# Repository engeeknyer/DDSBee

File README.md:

# DDSBee
## microcontrolled DDS oscillator circuit with XBee footprint

This directory contains the technical and constructive report for a microcontrolled DDS oscillator circuit. The onboard microcontroller allows the programming of the oscillator in a versatile way, using an instruction set close to the user’s language. The circuit is compatible with XBee footprint. Moreover the document also contains the user documentation and examples for proper use.
The device is intended to be a basic building block for a wide range of applications, thus easing the process of electronic system’s engineering. It exhibits remarkable degrees of flexibility, which makes it amenable to a wide range of possible applications.

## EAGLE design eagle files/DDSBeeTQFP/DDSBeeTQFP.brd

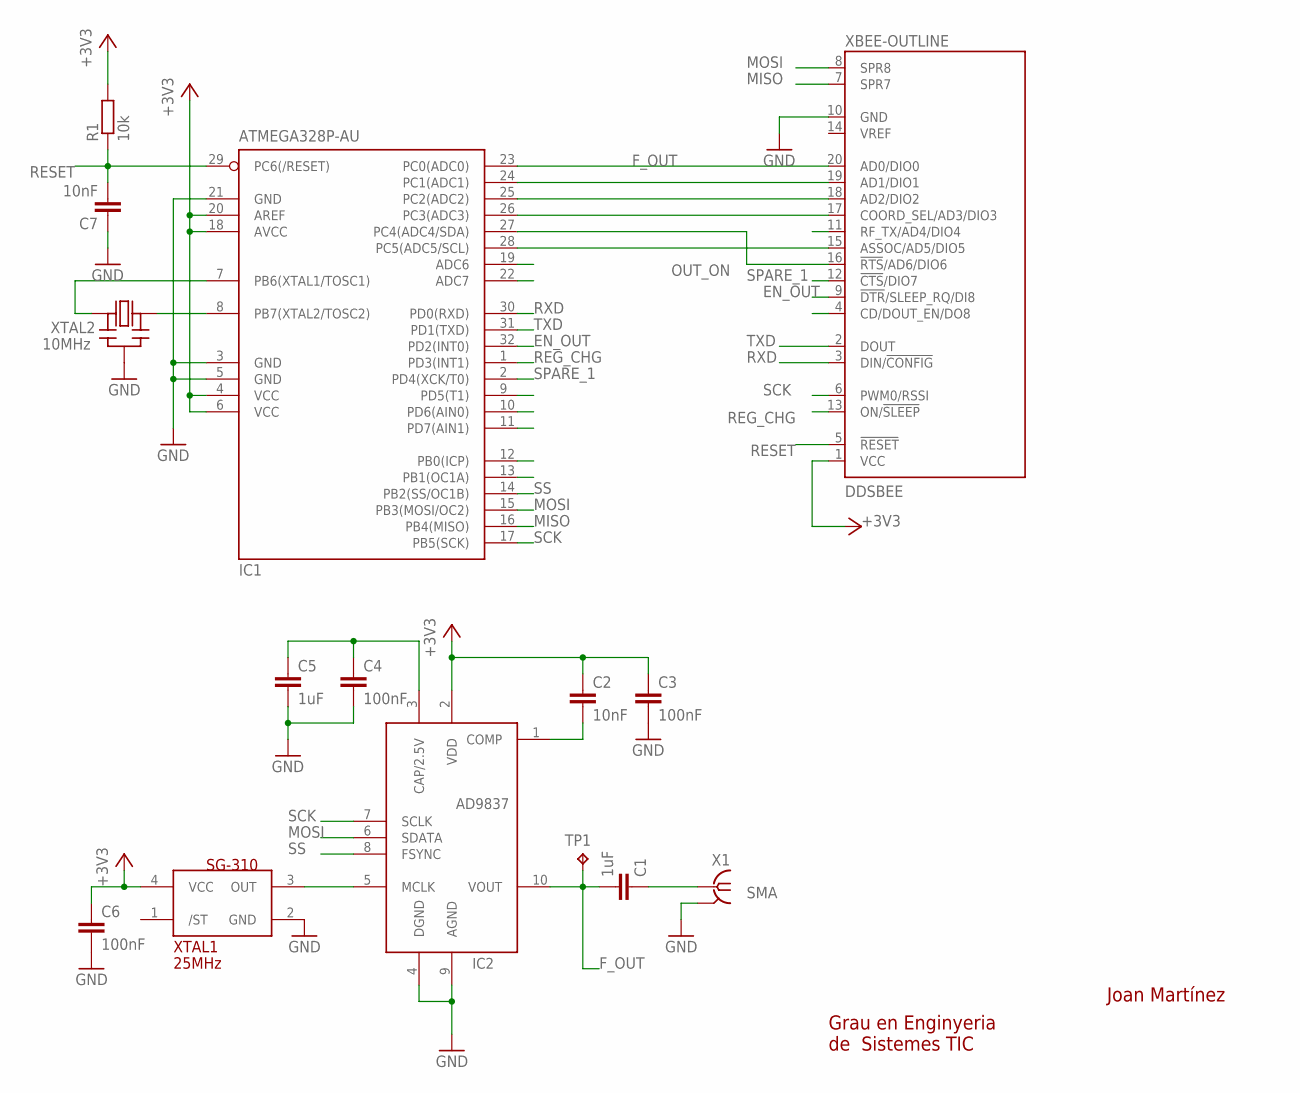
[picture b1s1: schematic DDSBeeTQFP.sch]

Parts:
C1, C5: 1uF; C0805
C2, C7: 10nF; C0805
C3, C4, C6: 100nF; C0805
DDSBEE: XBEE-OUTLINE; XBEE-PRO-DIM
IC1: ATMEGA328P-AU; TQFP32-08
IC2: AD9833; MSOP10
R1: 10k; R0805
TP1: TPTP15R; TP15R
X1: SMA; J502-ND-142-0701-871/876
XTAL1: 25MHz; EF241A
XTAL2: 10MHz; CERALOCK

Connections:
+3V3: C2.1, C3.1, C6.1, DDSBEE.1 (VCC), IC1.4 (VCC), IC1.6 (VCC), IC1.18 (AVCC), IC1.20 (AREF), IC2.2 (VDD), R1.2, XTAL1.4 (VCC)
EN_OUT: DDSBEE.9 (!DTR!/SLEEP_RQ/DI8), IC1.32 (PD2(INT0))
F_CON: C1.1, X1.1
F_OUT: C1.2, DDSBEE.20 (AD0/DIO0), IC1.23 (PC0(ADC0)), IC2.10 (VOUT), TP1.TP
GND: C3.2, C4.2, C5.2, C6.2, C7.1, DDSBEE.10 (GND), IC1.3 (GND), IC1.5 (GND), IC1.21 (GND), IC2.4 (DGND), IC2.9 (AGND), X1.G@1 (GND), X1.G@2 (GND), X1.G@3 (GND), X1.G@4 (GND), XTAL1.2 (GND), XTAL2.P$2 (GND)
MISO: DDSBEE.7 (SPR7), IC1.16 (PB4(MISO))
MOSI: DDSBEE.8 (SPR8), IC1.15 (PB3(MOSI/OC2)), IC2.6 (SDATA)
unnamed: IC1.8 (PB7(XTAL2/TOSC2)), XTAL2.P$3 (IN)
unnamed: C2.2, IC2.1 (COMP)
unnamed: C4.1, C5.1, IC2.3 (CAP/2.5V)
unnamed: IC1.7 (PB6(XTAL1/TOSC1)), XTAL2.P$1 (OUT)
unnamed: IC2.5 (MCLK), XTAL1.3 (OUT)
unnamed: DDSBEE.15 (ASSOC/AD5/DIO5), IC1.28 (PC5(ADC5/SCL))
unnamed: DDSBEE.19 (AD1/DIO1), IC1.24 (PC1(ADC1))
unnamed: DDSBEE.18 (AD2/DIO2), IC1.25 (PC2(ADC2))
unnamed: DDSBEE.17 (COORD_SEL/AD3/DIO3), IC1.26 (PC3(ADC3))
OUT_ON: DDSBEE.16 (!RTS!/AD6/DIO6), IC1.27 (PC4(ADC4/SDA))
REG_CHG: DDSBEE.13 (ON/!SLEEP), IC1.1 (PD3(INT1))
RESET: C7.2, DDSBEE.5 (!RESET), IC1.29 (PC6(/RESET)), R1.1
RXD: DDSBEE.3 (DIN/!CONFIG), IC1.30 (PD0(RXD))
SCK: DDSBEE.6 (PWM0/RSSI), IC1.17 (PB5(SCK)), IC2.7 (SCLK)
SPARE_1: DDSBEE.12 (!CTS!/DIO7), IC1.2 (PD4(XCK/T0))
SS: IC1.14 (PB2(SS/OC1B)), IC2.8 (FSYNC)
TXD: DDSBEE.2 (DOUT), IC1.31 (PD1(TXD))

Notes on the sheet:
Joan Martínez
Grau en Enginyeria de Sistemes TIC

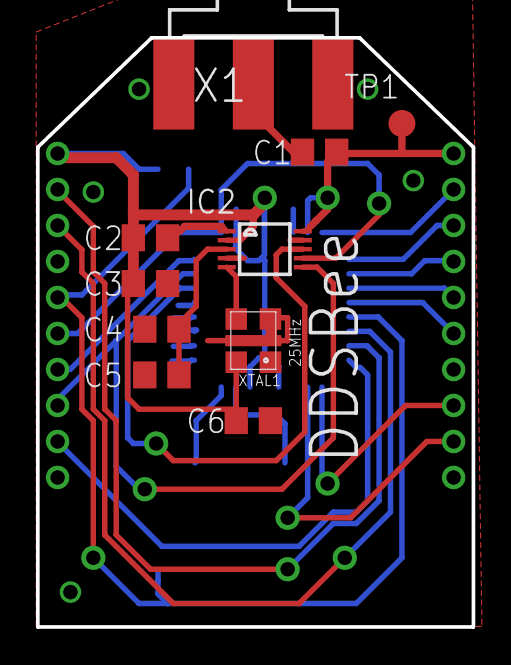
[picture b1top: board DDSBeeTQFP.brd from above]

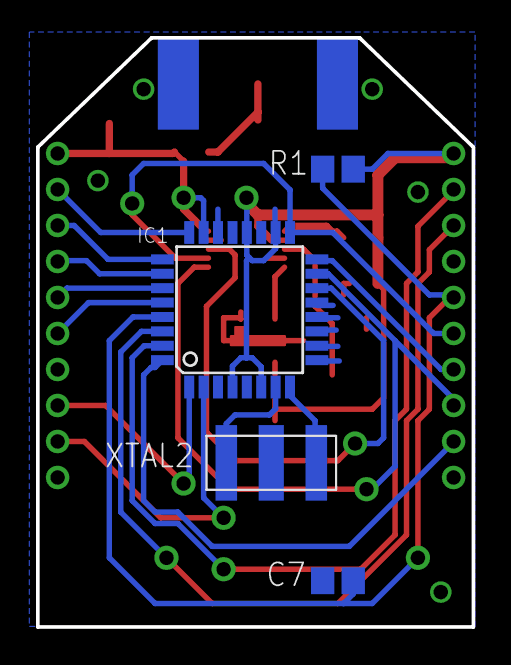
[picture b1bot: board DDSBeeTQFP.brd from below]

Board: 2 copper layers, 24.2 x 32.7 mm, 15 parts (4 on the bottom side), 24 nets.

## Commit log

2019-09-06 uploading source
2019-09-06 uploading eagle desing files
2019-09-16 create CERN license
2019-09-16 documentation license
